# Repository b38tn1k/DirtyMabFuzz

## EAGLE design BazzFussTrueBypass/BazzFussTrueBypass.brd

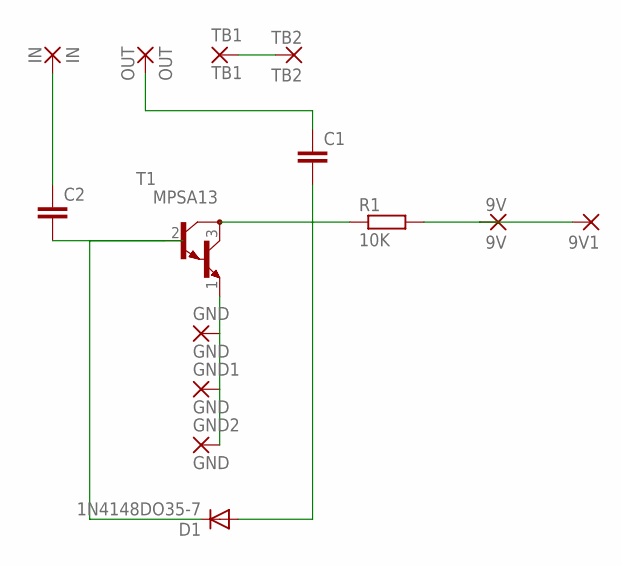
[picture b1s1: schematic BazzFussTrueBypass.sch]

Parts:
9V: 9V; 1,6/0,8
9V1: 1,6/0,8
C1, C2: C-EU025-025X050; C025-025X050
D1: 1N4148DO35-7; DO35-7
GND, GND1, GND2: GND; 1,6/0,8
IN: IN; 1,6/0,8
OUT: OUT; 1,6/0,8
R1: 10K; 0207/10
T1: MPSA13; TO92
TB1: TB1; 1,6/0,8
TB2: TB2; 1,6/0,8

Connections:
1N4148: C1.2, D1.A, R1.1, T1.3 (C)
9V: 9V.1, 9V1.1, R1.2
GND: GND.1, GND1.1, GND2.1, T1.1 (E)
IN: C2.1, IN.1
unnamed: TB1.1, TB2.1
unnamed: C2.2, D1.C, T1.2 (B)
OUT: C1.1, OUT.1

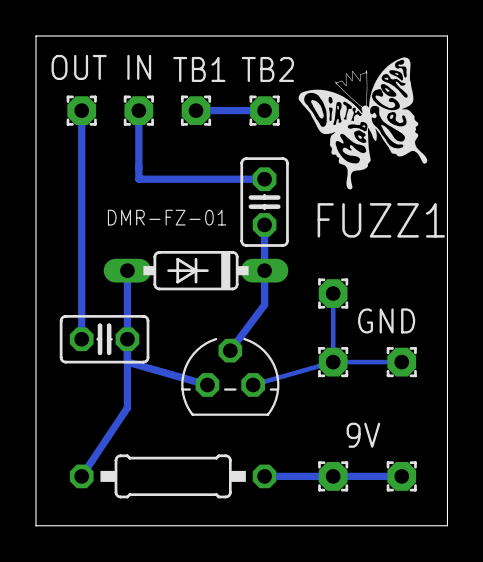
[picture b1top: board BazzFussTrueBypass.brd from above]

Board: 2 copper layers, 22.9 x 27.2 mm, 14 parts (0 on the bottom side), 7 nets.

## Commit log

2015-04-12 init
